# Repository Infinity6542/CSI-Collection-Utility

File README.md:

# CSI Collection Utility
This is just a with a custom PCB housing an ESP-32 that can be used to extract CSI data. I plan on using [Steven Hernandez's ESP-32 CSI extraction tool](https://github.com/StevenMHernandez/ESP32-CSI-Tool) to do this, obviously with a modified config. The data will be stored on an SD card and the entire system is battery powered. The PCB and battery is housed inside a case that has special cutouts for the switch, USB port, microSD card slot and the antenna. A cable should route from the ESP to the side of the case, which is where the antenna would be plugged in. 

Suitable for use in a microwave :) (just dont turn it on).

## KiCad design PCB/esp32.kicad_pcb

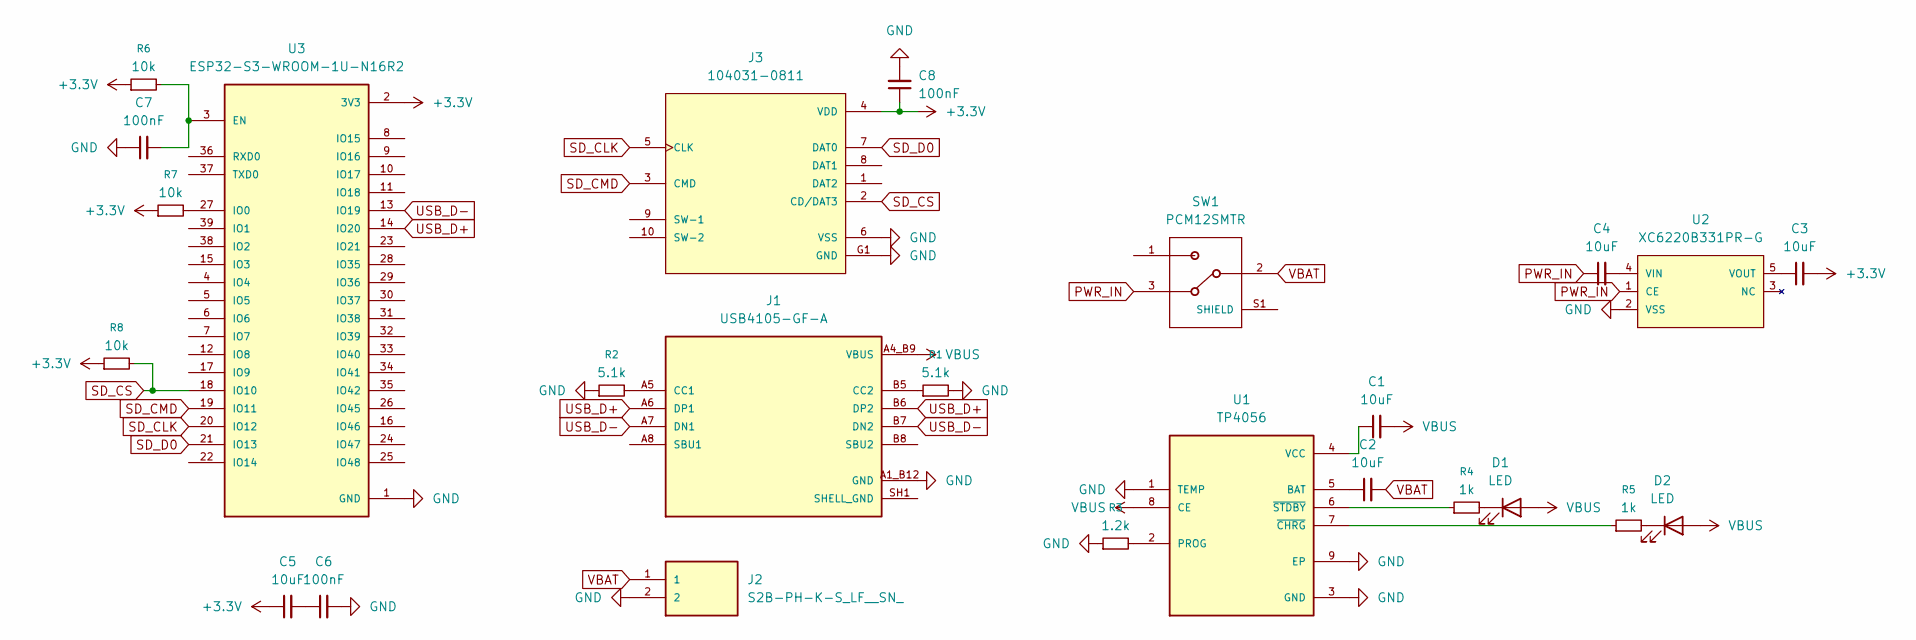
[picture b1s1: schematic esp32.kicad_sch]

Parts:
C1, C2, C3, C4, C5: 10uF; C_0603_1608Metric
C6, C7, C8: 100nF; C_0603_1608Metric
D1, D2: LED; LED_0603_1608Metric
J1: USB4105-GF-A; GCT_USB4105-GF-A; PARTREV B4
J2: S2B-PH-K-S_LF__SN_; JST_S2B-PH-K-S_LF__SN_
J3: 104031-0811; MOLEX_104031-0811; PARTREV B2
R1, R2: 5.1k; R_0603_1608Metric
R3: 1.2k; R_0603_1608Metric
R4, R5: 1k; R_0603_1608Metric
R6, R7, R8: 10k; R_0603_1608Metric
SW1: PCM12SMTR; SW_PCM12SMTR
U1: TP4056; SOP127P600X175-9N
U2: XC6220B331PR-G; XC6220B331PRG; MANUFACTURER_PART_NUMBER XC6220B331PR-G; DIGI-KEY_PART_NUMBER_1 893-1128-1-ND
U3: ESP32-S3-WROOM-1U-N16R2; XCVR_ESP32-S3-WROOM-1U-N16R2; PARTREV v1.1

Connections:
+3.3V: C3.2, C5.1, C8.1, J3.4 (VDD), R6.1, R7.1, R8.1, U3.2 (3V3)
GND: C6.2, C7.1, C8.2, J1.A1_B12 (GND), J1.B1_A12 (GND), J2.2, J3.6 (VSS), J3.G1 (GND), J3.G2 (GND), J3.G3 (GND), J3.G4 (GND), R1.2, R2.1, R3.1, U1.1 (TEMP), U1.3 (GND), U1.9 (EP), U2.2 (VSS), U2.6, U2.7, U3.1 (GND), U3.40 (GND), U3.41_1 (GND), U3.41_2 (GND), U3.41_3 (GND), U3.41_4 (GND), U3.41_5 (GND), U3.41_6 (GND), U3.41_7 (GND), U3.41_8 (GND), U3.41_9 (GND), U3.41_10, U3.41_11, U3.41_12, U3.41_13, U3.41_14, U3.41_15, U3.41_16, U3.41_17, U3.41_18, U3.41_19, U3.41_20, U3.41_21
unnamed: C5.2, C6.1
unnamed: D1.1 (K), R4.2
unnamed: D2.1 (K), R5.2
unnamed: J1.A5 (CC1), R2.2
unnamed: J1.B5 (CC2), R1.1
unnamed: SW1.S1 (SHIELD), SW1.S2 (SHIELD), SW1.S3 (SHIELD), SW1.S4 (SHIELD)
unnamed: C2.1, U1.5 (BAT)
unnamed: R3.2, U1.2 (PROG)
unnamed: C1.1, U1.4 (VCC)
unnamed: R5.1, U1.7 (~CHRG)
unnamed: R4.1, U1.6 (~STDBY)
unnamed: C4.2, U2.4 (VIN)
unnamed: C3.1, U2.5 (VOUT)
unnamed: C7.2, R6.2, U3.3 (EN)
unnamed: R7.2, U3.27 (IO0)
PWR_IN: C4.1, SW1.3, U2.1 (CE)
SD_CLK: J3.5 (CLK), U3.20 (IO12)
SD_CMD: J3.3 (CMD), U3.19 (IO11)
SD_CS: J3.2 (CD/DAT3), R8.2, U3.18 (IO10)
SD_D0: J3.7 (DAT0), U3.21 (IO13)
SHELL_GND: J1.SH1 (SHELL_GND), J1.SH2 (SHELL_GND), J1.SH3 (SHELL_GND), J1.SH4 (SHELL_GND)
USB_D+: J1.A6 (DP1), J1.B6 (DP2), U3.14 (IO20)
USB_D-: J1.A7 (DN1), J1.B7 (DN2), U3.13 (IO19)
VBAT: C2.2, J2.1, SW1.2
VBUS: C1.2, D1.2 (A), D2.2 (A), J1.A4_B9 (VBUS), J1.B4_A9 (VBUS), U1.8 (CE)

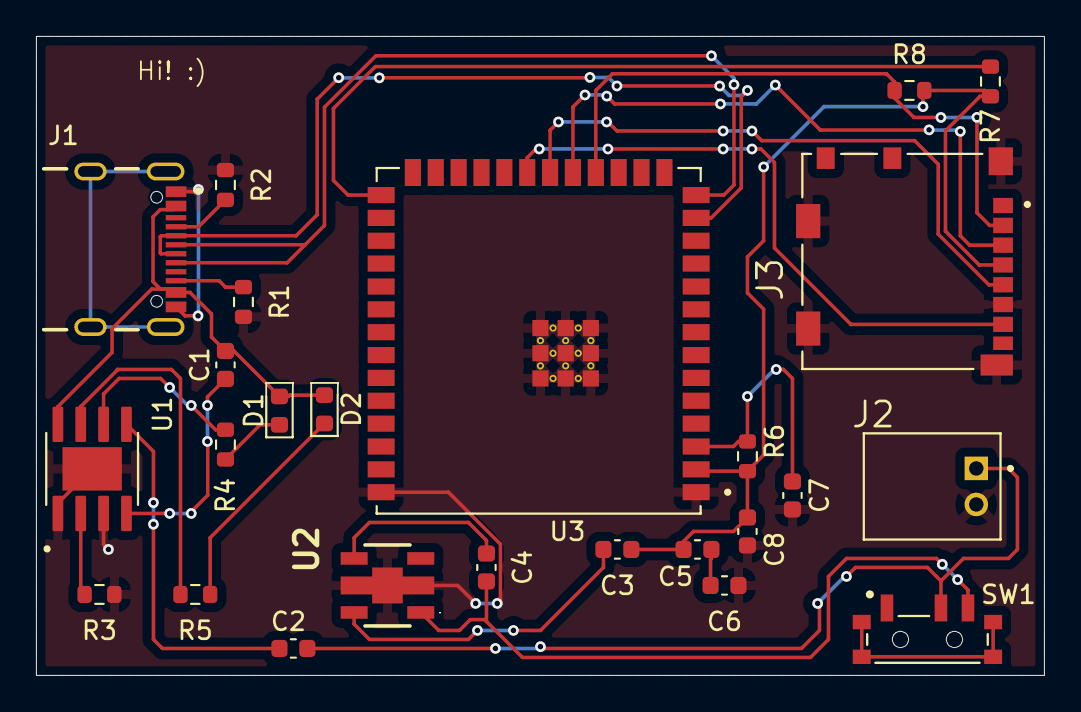
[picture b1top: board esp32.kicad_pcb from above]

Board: 2 copper layers, 56.0 x 35.5 mm, 25 parts (0 on the bottom side), 27 nets.

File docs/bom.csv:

Designator,Quantity,Value,Cost
"C1, C2, C3, C4, C5",5,10uF,
"C6, C7, C8",3,100nF,
D1,1,LED,
D2,1,LED,
J1,1,USB4105-GF-A,
J2,1,S2B-PH-K-S_LF__SN_,
J3,1,104031-0811,
"R1, R2",2,5.1k,
R3,1,1.2k,
"R4, R5",2,1k,
"R6, R7, R8",3,10k,
SW1,1,PCM12SMTR,
U1,1,TP4056,
U2,1,XC6220B331PR-G,
U3,1,ESP32-S3-WROOM-1U-N16R2,
N/A,1,Lid,
N/A,1,Body,

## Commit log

2025-12-15 Start
2025-12-15 Update README with images
2025-12-15 Update BOM
2025-12-17 Fix BOM
2025-12-25 Fixed incorrect price from JLPCB
2025-12-25 Adjust currency exchange

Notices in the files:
parts and their libraries:
COPYRIGHT: Copyright (C) 2022 Ultra Librarian. All rights reserved.
